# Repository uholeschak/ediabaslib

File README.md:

## Project Description

.NET BMW and VAG Ediabas interpreter library.

# Features
This .NET assembly is small and fast replacement for the BMW and VAG Ediabas toolset.  
It runs on all platforms that support .NET framework (Windows, Windows CE, Mono).  
The code is speed optimized, but improved for multiple calls of the same job.  
This means the first job call is slow and the next are faster.

The library can directly read and interpret `.GRP` and `.PRG` files, the internal interface is similar to the EDIABAS API or the Tool32.exe GUI interface.  
At the moment the D-CAN, BMW-FAST, KWP-2000*, KWP-2000 BMW, DS2, DS1, Concept 3, ISO9141 (Concept 2) and Concept 1 concepts are supported. If you send me EDIABAS log files from other concepts I could add them if possible.  
Now a variant that can be used with cars from the VAG group has been released, but it requires an adapter with the [Replacement firmware for ELM327](docs/Replacement_firmware_for_ELM327.md). In this mode, the protocols KWP2000, KWP1281 and TP2.0 are supported (cars until 4.2012).  

For testing, there is a console application [EdiabasTest](docs/EdiabasTest_parameters.md) with command line parameters.

**More information can be found in the [Documentation](docs/Documentation.md) section.**  

**These are expert tools, I have no time for detailed support. Please search the internet for _EDIABAS_, _Tool32_, _INPA_, _ISTA-D_, _ISTA-P_ e.g. or use forums to get help.**

If you want to support the development you can donate a small amount.  

# Binary Compatibility
A binary compatible `api32.dll` wrapper is included, it's possible to replace the existing EDIABAS `api32.dll` with the EdiabasLib `api32.dll` and the applications still work! (The DLL requires [.NET Framework 4.8.1 Runtime](https://dotnet.microsoft.com/en-us/download/dotnet-framework/net481) or higher, [.NET 10.0 Desktop Runtime](https://dotnet.microsoft.com/en-us/download/dotnet/10.0) and [VS C++ Runtime 64 bit](https://aka.ms/vc14/vc_redist.x64.exe) or [VS C++ Runtime 32 bit](https://aka.ms/vc14/vc_redist.x86.exe) to be installed)  
This has been tested with Tool32, INPA and Rheingold. Since EdiabasNet ignores the `EDIABAS.INI` file you have to put your own `EdiabasLib.config` file in the `api32.dll` directory.
A compatible `apiNET32.dll` is also available, so it should be easy to port existing .NET applications that use the original EDIABAS library.

# Android
Now there is also included a library that works with Mono for Android. For communication, either FTDI USB or Bluetooth Serial Port Protocol (SSP) protocol can be used.

### Deep OBD
Additionally an Android application _[Deep OBD](docs/Deep_OBD_for_BMW_and_VAG.md)_ exists, that is configurable via [XML](docs/Page_specification.md). Generation of XML code can be simplified with the integrated configuration generator.  
Download app from Google Play: [https://play.google.com/store/apps/details?id=de.holeschak.bmw_deep_obd](https://play.google.com/store/apps/details?id=de.holeschak.bmw_deep_obd)  
  
Rated by updatestar.com: [https://deep-obd.updatestar.com](https://deep-obd.updatestar.com)  

_Deep OBD for BMW and VAG_ supports several OBD II adapters:
* Standard FTDI based USB "INPA compatible" D-CAN/K-Line adapters (all protocols)
* ELM327 Bluetooth and WiFi adapters based on PIC18F2480 microcontroller (no MCP2515 chip). Recommended ELM327 versions are 1.4b, 1.5 and origin 2.1. (D-CAN protocol only)
* ELM327 Bluetooth adapters based on PIC18F25K80 microcontroller with [Replacement firmware for ELM327](docs/Replacement_firmware_for_ELM327.md) D-CAN and K-Line (all protocols, including VAG KWP2000, KWP1281 and TP2.0). Programmed adapters are now available.

More details can be found here: [Supported adapter types](docs/AdapterTypes.md)

* Custom [Bluetooth D-CAN/K-Line adapter](docs/Build_Bluetooth_D-CAN_adapter.md) (BMW-FAST protocol over D-CAN and K-Line)
* [ENET WiFi adapters](docs/ENET_WiFi_Adapter.md) (for BMW F-models)

https://holeschak.de/BmwDeepObd/594.apk

### Android Auto
[Android Auto](docs/Deep_OBD_for_BMW_and_VAG.md#android-auto) is now available in the release version of _[Deep OBD](docs/Deep_OBD_for_BMW_and_VAG.md)_.

# Hints
At the moment most BEST/1 commands are implemented, but a few are still missing, which seem to be not required in the current ECU files.  
The implemented commands are automatically tested and compared with EDIABAS output.

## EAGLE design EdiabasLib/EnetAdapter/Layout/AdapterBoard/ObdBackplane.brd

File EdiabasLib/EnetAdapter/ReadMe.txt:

Build OpenWrt:
--------------
Pepare build system according to:
https://wiki.openwrt.org/doc/howto/build
copy diffconfig to build directory
copy patches/770-group_key_timeout.patch to package/network/services/hostapd/patches
copy patches/0303-rt3052-disable-ports.patch to target/linux/ramips/patches-3.18

cp diffconfig .config
make defconfig
make
("make target/linux/clean" and "make target/linux/compile" builds the kernel only)

If download of packages fails build with
make V=s
and copy the missing files to the dl directory.

copy imagebuilder from bin new location
extract imagebilder tar -xvjf ...
copy files directory and build.sh to imagebilder build directory

sh build.sh

Debuging hostadp:
-----------------
make menuconfig
(make kernel_menuconfig for kernel modiifications)
Network->wap-supplicant->Minimum debug message priority: 0
Debug according to
https://wiki.openwrt.org/doc/devel/debugging
kill `cat /var/run/wifi-phy0.pid` until hostadp finally dies.
iw dev wlan0 del
iw phy phy0 interface add wlan0 type managed
/usr/sbin/hostapd -ddddddd -P /var/run/wifi-phy0.pid /var/run/hostapd-phy0.conf > /tmp/log.txt &

Flash firmware with uboot:
--------------------------
Set adapter ip address to 192.168.1.55
add arp table entry:
arp -s 192.168.1.109 00-AA-BB-CC-DD-10 192.168.1.55
Start uboot and select 2
local ip: 192.168.1.109
server ip: 192.168.1.55
file: openwrt-15.05-ramips-rt305x-a5-v11-squashfs-sysupgrade.bin
Start tftp server

Update QualComm factory firmware:
---------------------------------
Copy uboot.img and mini.bin to USB stick
Set network adapter to 192.168.100.10/255.255.255.0 or 192.168.169.10/255.255.255.0
------------------------------
as admin:
netsh interface ip set address "Ethernet 2" static 192.168.100.10 255.255.255.0 192.168.100.10
or
netsh interface ip set address "Ethernet 2" static 192.168.169.10 255.255.255.0 192.168.169.10
------------------------------
insert USB stick into the router

telnet 192.168.100.1 or 192.168.169.1
login: admin/admin
mount /dev/sda1 /mnt
ls /mnt
uboot.img and mini.bin should be visible
mtd_write write /mnt/uboot.img Bootloader
mtd_write write /mnt/mini.bin Kernel
reboot
remove USB stick

------------------------------
as admin:
netsh interface ip set address "Ethernet 2" static 192.168.100.10 255.255.255.0 192.168.100.10
------------------------------

miniweb:
--------
copy openwrt-15.05-ramips-rt305x-a5-v11-squashfs-sysupgrade.bin to the miniweb htdocs directory
start miniweb.exe
telnet 192.168.100.1
wget -P /tmp http://192.168.100.10:8000/openwrt-15.05-ramips-rt305x-a5-v11-squashfs-sysupgrade.bin
sysupgrade -v -n /tmp/openwrt-15.05-ramips-rt305x-a5-v11-squashfs-sysupgrade.bin

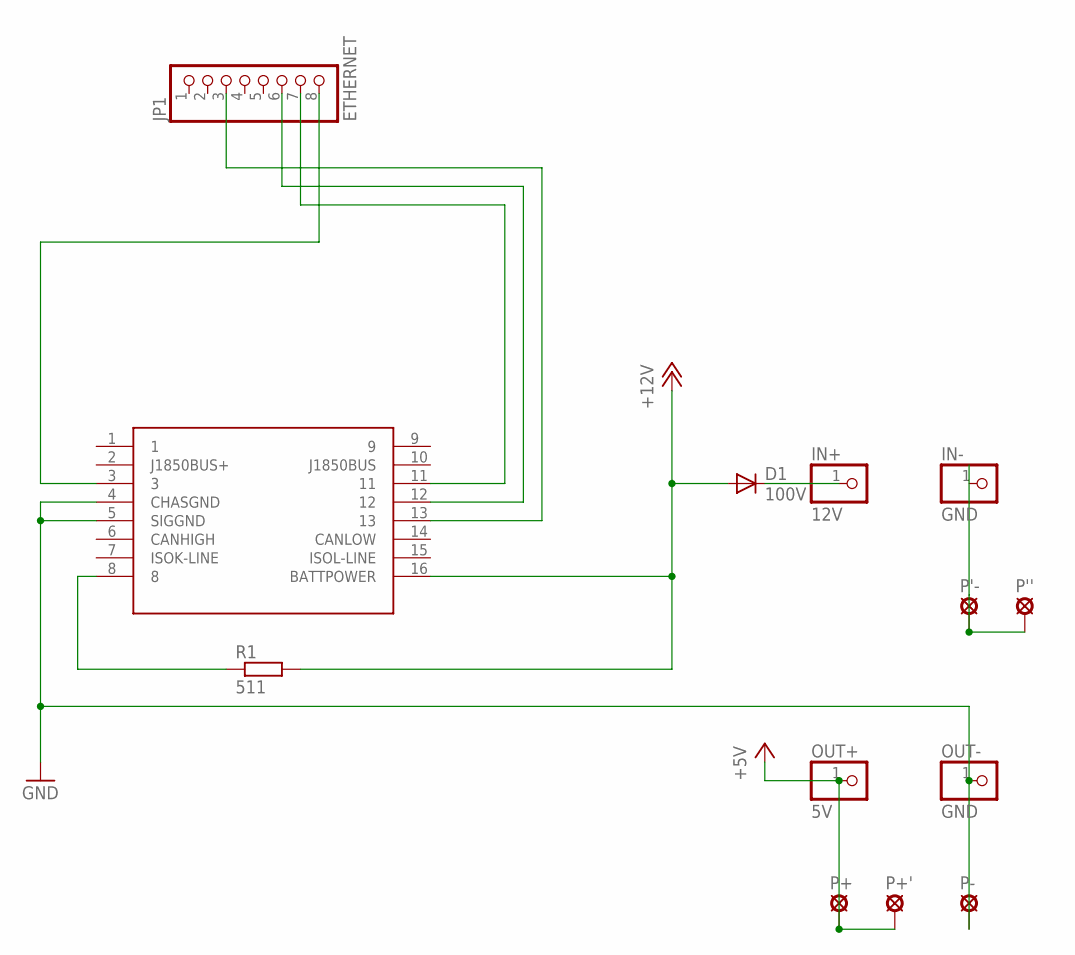
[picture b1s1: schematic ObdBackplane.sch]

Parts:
D1: 100V; DO214AC
IN+: 12V; 1X01
IN-: GND; 1X01
JP1: ETHERNET; 1X08M-1MM
OBDII: OBDII
OUT+: 5V; 1X01
OUT-: GND; 1X01
P'': SE14
P'-: SE14
P+: SE14
P+': SE14
P-: SE14
R1: 511; R2512

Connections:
+5V: OUT+.1, P+.MP, P+'.MP
+12V: D1.A, OBDII.16 (BATTPOWER), R1.2
GND: OBDII.4 (CHASGND), OBDII.5 (SIGGND), OUT-.1, P-.MP
GND2: IN-.1, P''.MP, P'-.MP
unnamed: D1.C, IN+.1
unnamed: OBDII.8, R1.1
unnamed: JP1.8, OBDII.3
unnamed: JP1.6, OBDII.12
unnamed: JP1.3, OBDII.13
unnamed: JP1.7, OBDII.11

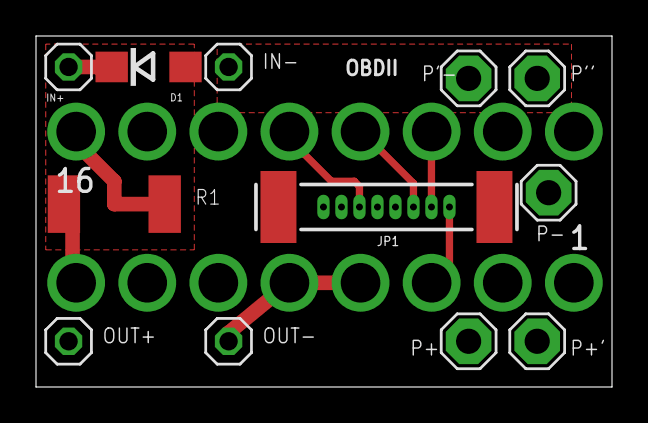
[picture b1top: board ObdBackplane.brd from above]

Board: 2 copper layers, 32.0 x 19.5 mm, 13 parts (0 on the bottom side), 10 nets.

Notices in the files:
parts and their libraries:
SparkFun-Connectors: Licensing: Creative Commons ShareAlike 4.0 International - https://creativecommons.org/licenses/by-sa/4.0
